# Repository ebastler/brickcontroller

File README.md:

# brickcontroller
ESP32 based PCB to control LED-bricks

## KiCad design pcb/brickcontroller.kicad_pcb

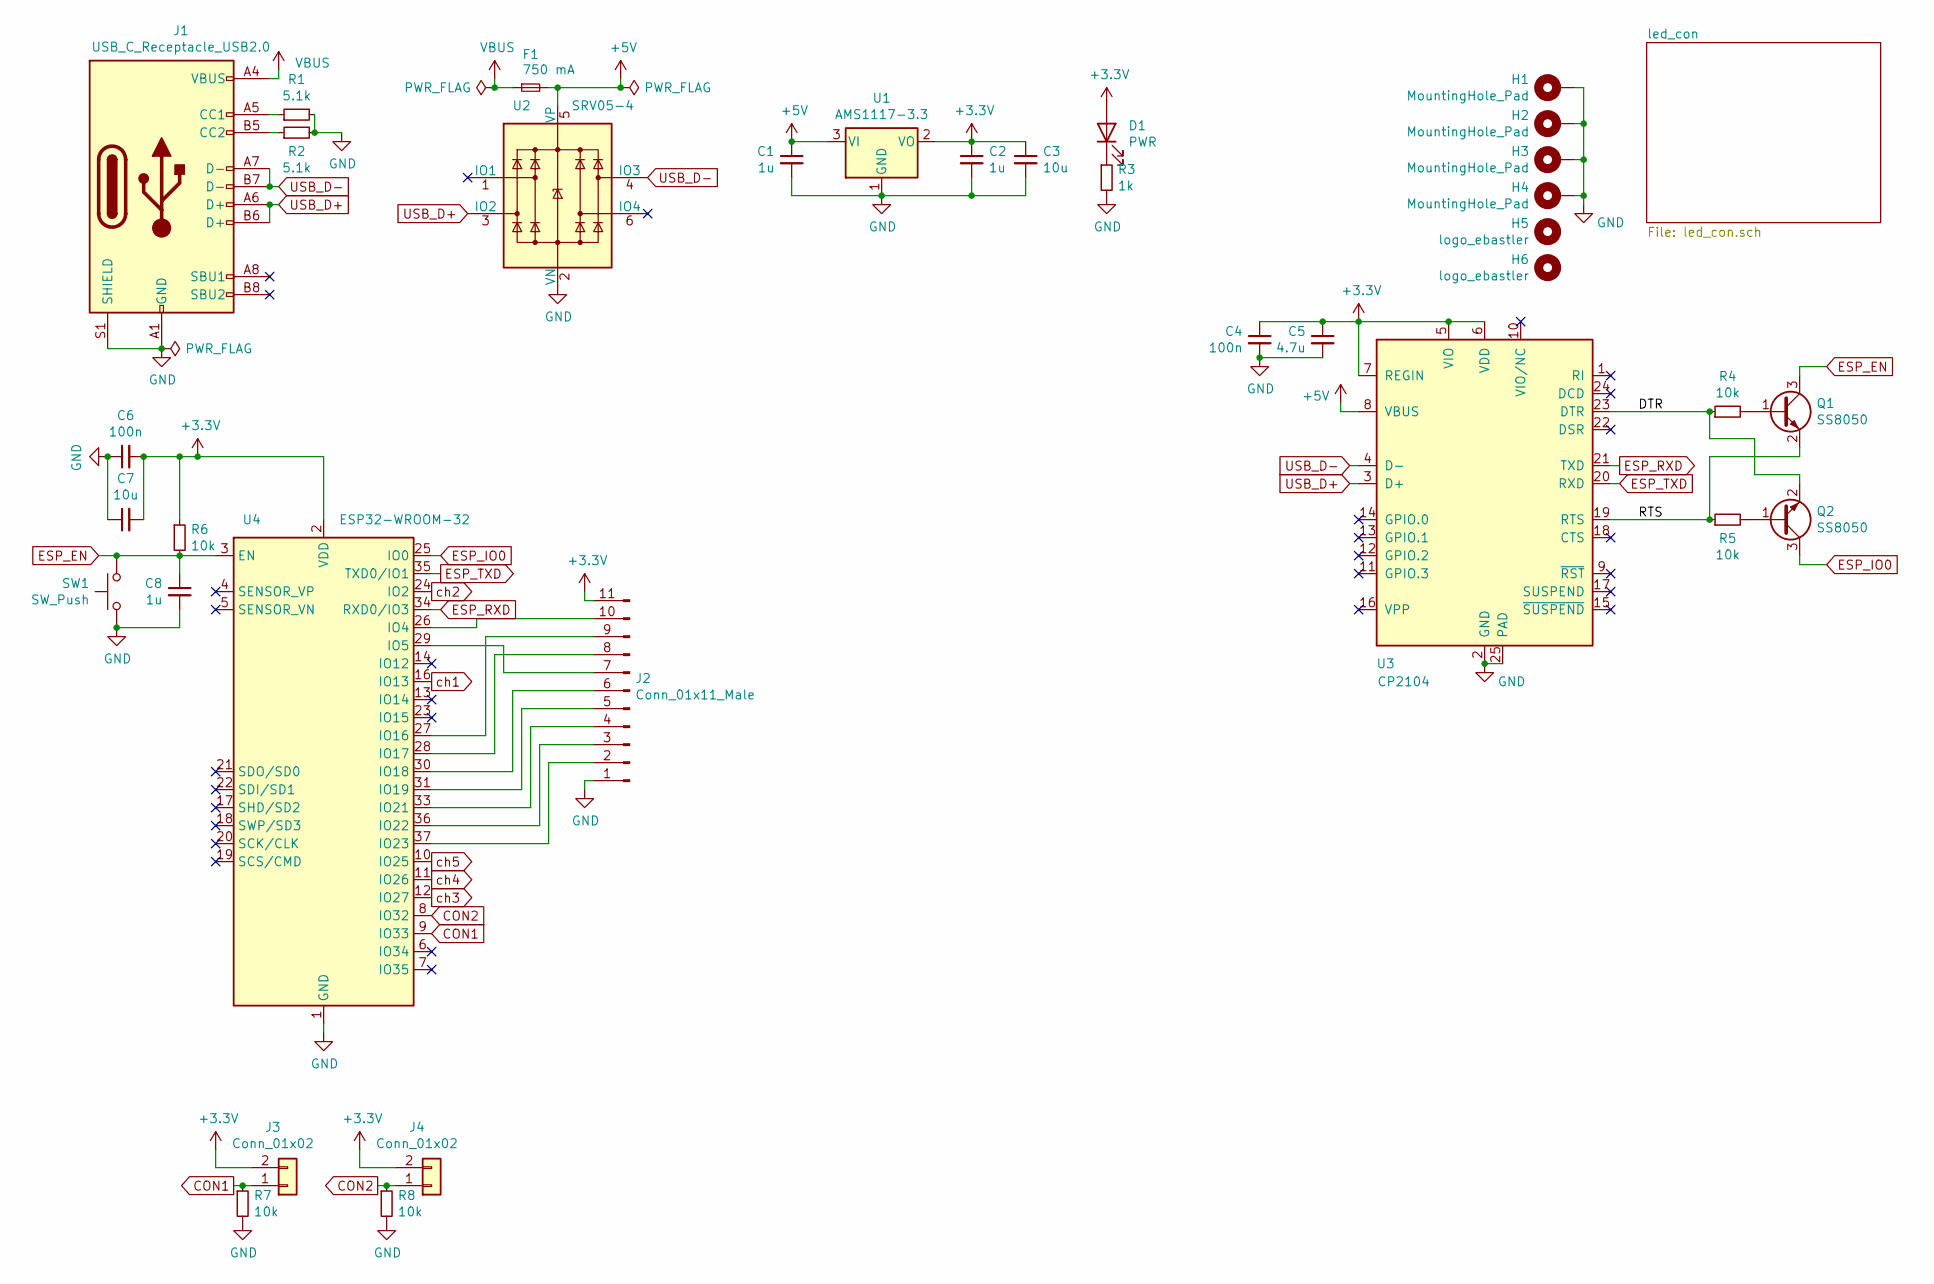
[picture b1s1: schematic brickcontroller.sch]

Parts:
C1, C2, C8: 1u; C_0603_1608Metric; LCSC C15849
C3, C7: 10u; C_0603_1608Metric; LCSC C19702
C4, C6: 100n; C_0603_1608Metric; LCSC C14663
C5: 4.7u; C_0603_1608Metric; LCSC C19666
D1: PWR; LED_0603_1608Metric; LCSC C72038
F1: 750 mA; Fuse_0603_1608Metric; LCSC C20792
H1, H2, H3, H4: MountingHole_Pad; MountingHole_3.2mm_M3_Pad_Via
H5: logo_ebastler; logo_silk_7p5
H6: logo_ebastler; brick
J1: USB_C_Receptacle_USB2.0; USB_C_Receptacle_HRO_TYPE-C-31-M-12; LCSC C165948
J2: Conn_01x11_Male; PinSocket_1x11_P2.54mm_Vertical
J3, J4: Conn_01x02; Molex_PicoBlade_53047-0210_1x02_P1.25mm_Vertical
Q1, Q2: SS8050; SOT-23; LCSC C2150
R1, R2: 5.1k; R_0402_1005Metric; LCSC C25905
R3: 1k; R_0603_1608Metric; LCSC C21190
R4, R5, R6, R7, R8: 10k; R_0603_1608Metric; LCSC C25804
SW1: SW_Push; SW_SPST_SKQG_WithoutStem; LCSC C318884
U1: AMS1117-3.3; SOT-223-3_TabPin2; LCSC C6186
U2: SRV05-4; SOT-23-6; LCSC C85364
U3: CP2104; QFN-24-1EP_4x4mm_P0.5mm_EP2.6x2.6mm; LCSC C47742
U4: ESP32-WROOM-32; LCSC C82899

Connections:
+3V3: C2.1, C3.1, C4.1, C5.1, C6.2, C7.2, D1.2 (A), J2.11, J3.2, J4.2, R6.1, U1.2 (VO), U3.5 (VIO), U3.6 (VDD), U3.7 (REGIN), U4.2 (VDD); also elsewhere on the board
+5V: C1.1, F1.2, U1.3 (VI), U2.5 (VP), U3.8 (VBUS)
/DTR: Q2.2 (E), R4.1, U3.23 (DTR)
/RTS: Q1.2 (E), R5.1, U3.19 (RTS)
CON1: J3.1, R7.1, U4.9 (IO33)
CON2: J4.1, R8.1, U4.8 (IO32)
ESP_EN: C8.1, Q1.3 (C), R6.2, SW1.2, U4.3 (EN)
ESP_IO0: Q2.3 (C), U4.25 (IO0)
ESP_RXD: U3.21 (TXD), U4.34 (RXD0/IO3)
ESP_TXD: U3.20 (RXD), U4.35 (TXD0/IO1)
GND: C1.2, C2.2, C3.2, C4.2, C5.2, C6.1, C7.1, C8.2, H1.1, H2.1, H3.1, H4.1, J1.A1 (GND), J1.A12 (GND), J1.B1 (GND), J1.B12 (GND), J1.S1 (SHIELD), J2.1, R1.2, R2.2, R3.2, R7.2, R8.2, SW1.1, U1.1 (GND), U2.2 (VN), U3.2 (GND), U3.25 (PAD), U4.1 (GND), U4.15 (GND), U4.38 (GND), U4.39 (GND); also elsewhere on the board
unnamed: D1.1 (K), R3.1
unnamed: J1.A5 (CC1), R1.1
unnamed: J1.B5 (CC2), R2.1
unnamed: J2.2, U4.37 (IO23)
unnamed: J2.3, U4.36 (IO22)
unnamed: J2.4, U4.33 (IO21)
unnamed: J2.5, U4.31 (IO19)
unnamed: J2.6, U4.30 (IO18)
unnamed: J2.7, U4.29 (IO5)
unnamed: J2.8, U4.28 (IO17)
unnamed: J2.9, U4.27 (IO16)
unnamed: J2.10, U4.26 (IO4)
unnamed: Q1.1 (B), R4.2
unnamed: Q2.1 (B), R5.2
USB_D+: J1.A6 (D+), J1.B6 (D+), U2.3 (IO2), U3.3 (D+)
USB_D-: J1.A7 (D-), J1.B7 (D-), U2.4 (IO3), U3.4 (D-)
VBUS: F1.1, J1.A4 (VBUS), J1.A9 (VBUS), J1.B4 (VBUS), J1.B9 (VBUS)
ch1: U4.16 (IO13); also elsewhere on the board
ch2: U4.24 (IO2); also elsewhere on the board
ch3: U4.12 (IO27); also elsewhere on the board
ch4: U4.11 (IO26); also elsewhere on the board
ch5: U4.10 (IO25); also elsewhere on the board

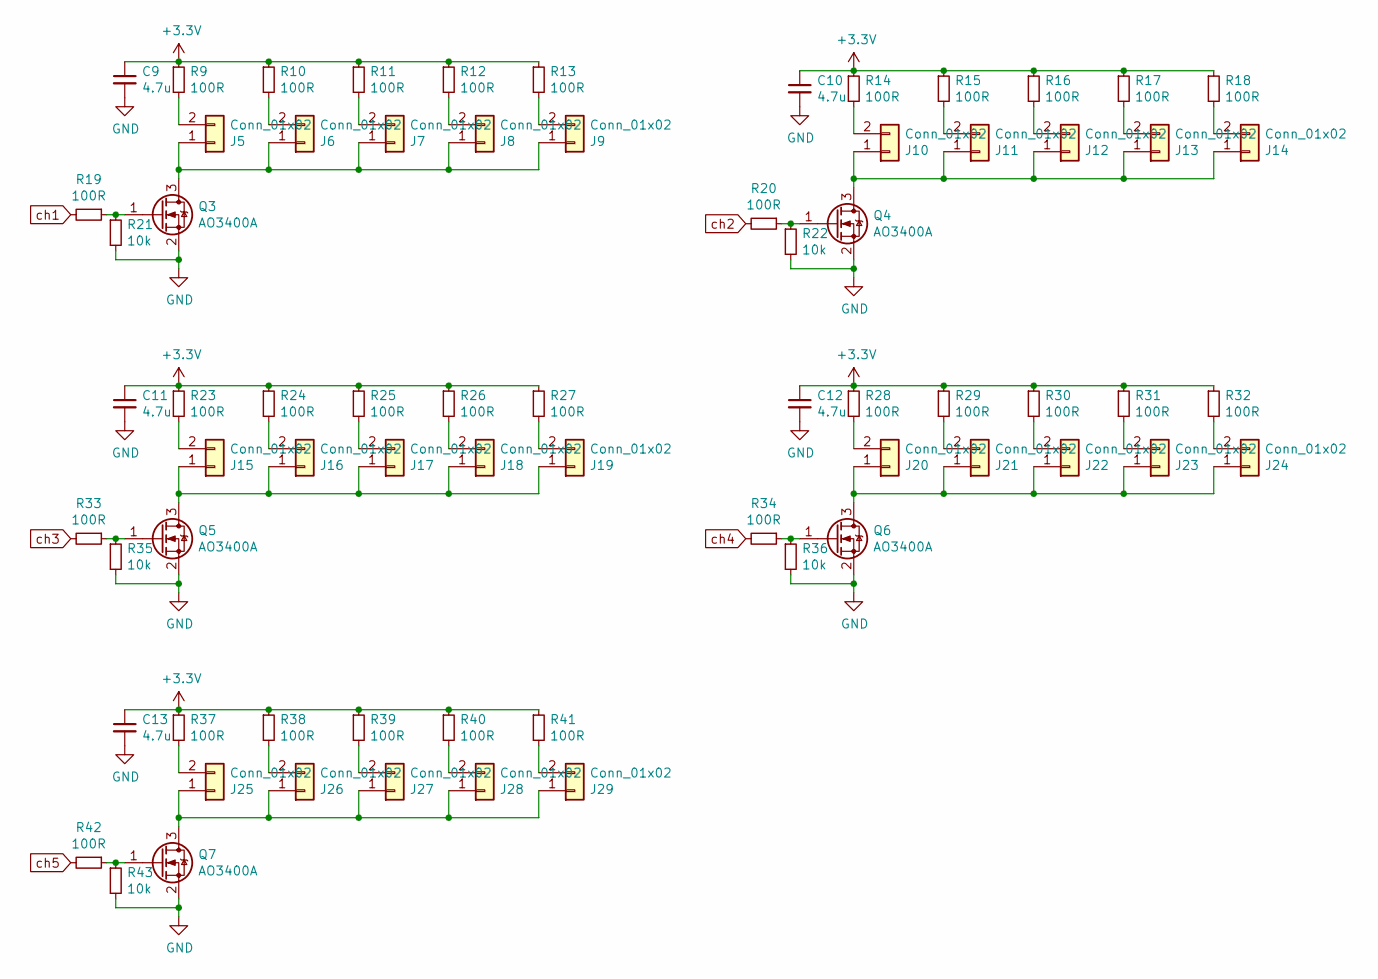
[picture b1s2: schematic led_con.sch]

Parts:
C9, C10, C11, C12, C13: 4.7u; C_0603_1608Metric; LCSC C19666
J5, J6, J7, J8, J9, J10, J11, J12, J13, J14, J15, J16, J17, J18, J19, J20, J21, J22, J23, J24, J25, J26, J27, J28, J29: Conn_01x02; Molex_PicoBlade_53047-0210_1x02_P1.25mm_Vertical
Q3, Q4, Q5, Q6, Q7: AO3400A; SOT-23; LCSC C347475
R9, R10, R11, R12, R13, R14, R15, R16, R17, R18, R19, R20, R23, R24, R25, R26, R27, R28, R29, R30, R31, R32, R33, R34, R37, R38, R39, R40, R41, R42: 100R; R_0603_1608Metric; LCSC C22775
R21, R22, R35, R36, R43: 10k; R_0603_1608Metric; LCSC C25804

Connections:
+3V3: C9.1, C10.1, C11.1, C12.1, C13.1, R9.1, R10.1, R11.1, R12.1, R13.1, R14.1, R15.1, R16.1, R17.1, R18.1, R23.1, R24.1, R25.1, R26.1, R27.1, R28.1, R29.1, R30.1, R31.1, R32.1, R37.1, R38.1, R39.1, R40.1, R41.1; also elsewhere on the board
GND: C9.2, C10.2, C11.2, C12.2, C13.2, Q3.2 (S), Q4.2 (S), Q5.2 (S), Q6.2 (S), Q7.2 (S), R21.2, R22.2, R35.2, R36.2, R43.2; also elsewhere on the board
unnamed: J5.1, J6.1, J7.1, J8.1, J9.1, Q3.3 (D)
unnamed: J5.2, R9.2
unnamed: J6.2, R10.2
unnamed: J7.2, R11.2
unnamed: J8.2, R12.2
unnamed: J9.2, R13.2
unnamed: J10.1, J11.1, J12.1, J13.1, J14.1, Q4.3 (D)
unnamed: J10.2, R14.2
unnamed: J11.2, R15.2
unnamed: J12.2, R16.2
unnamed: J13.2, R17.2
unnamed: J14.2, R18.2
unnamed: J15.1, J16.1, J17.1, J18.1, J19.1, Q5.3 (D)
unnamed: J15.2, R23.2
unnamed: J16.2, R24.2
unnamed: J17.2, R25.2
unnamed: J18.2, R26.2
unnamed: J19.2, R27.2
unnamed: J20.1, J21.1, J22.1, J23.1, J24.1, Q6.3 (D)
unnamed: J20.2, R28.2
unnamed: J21.2, R29.2
unnamed: J22.2, R30.2
unnamed: J23.2, R31.2
unnamed: J24.2, R32.2
unnamed: J25.1, J26.1, J27.1, J28.1, J29.1, Q7.3 (D)
unnamed: J25.2, R37.2
unnamed: J26.2, R38.2
unnamed: J27.2, R39.2
unnamed: J28.2, R40.2
unnamed: J29.2, R41.2
unnamed: Q3.1 (G), R19.1, R21.1
unnamed: Q4.1 (G), R20.1, R22.1
unnamed: Q5.1 (G), R33.1, R35.1
unnamed: Q6.1 (G), R34.1, R36.1
unnamed: Q7.1 (G), R42.1, R43.1
ch1: R19.2; also elsewhere on the board
ch2: R20.2; also elsewhere on the board
ch3: R33.2; also elsewhere on the board
ch4: R34.2; also elsewhere on the board
ch5: R42.2; also elsewhere on the board

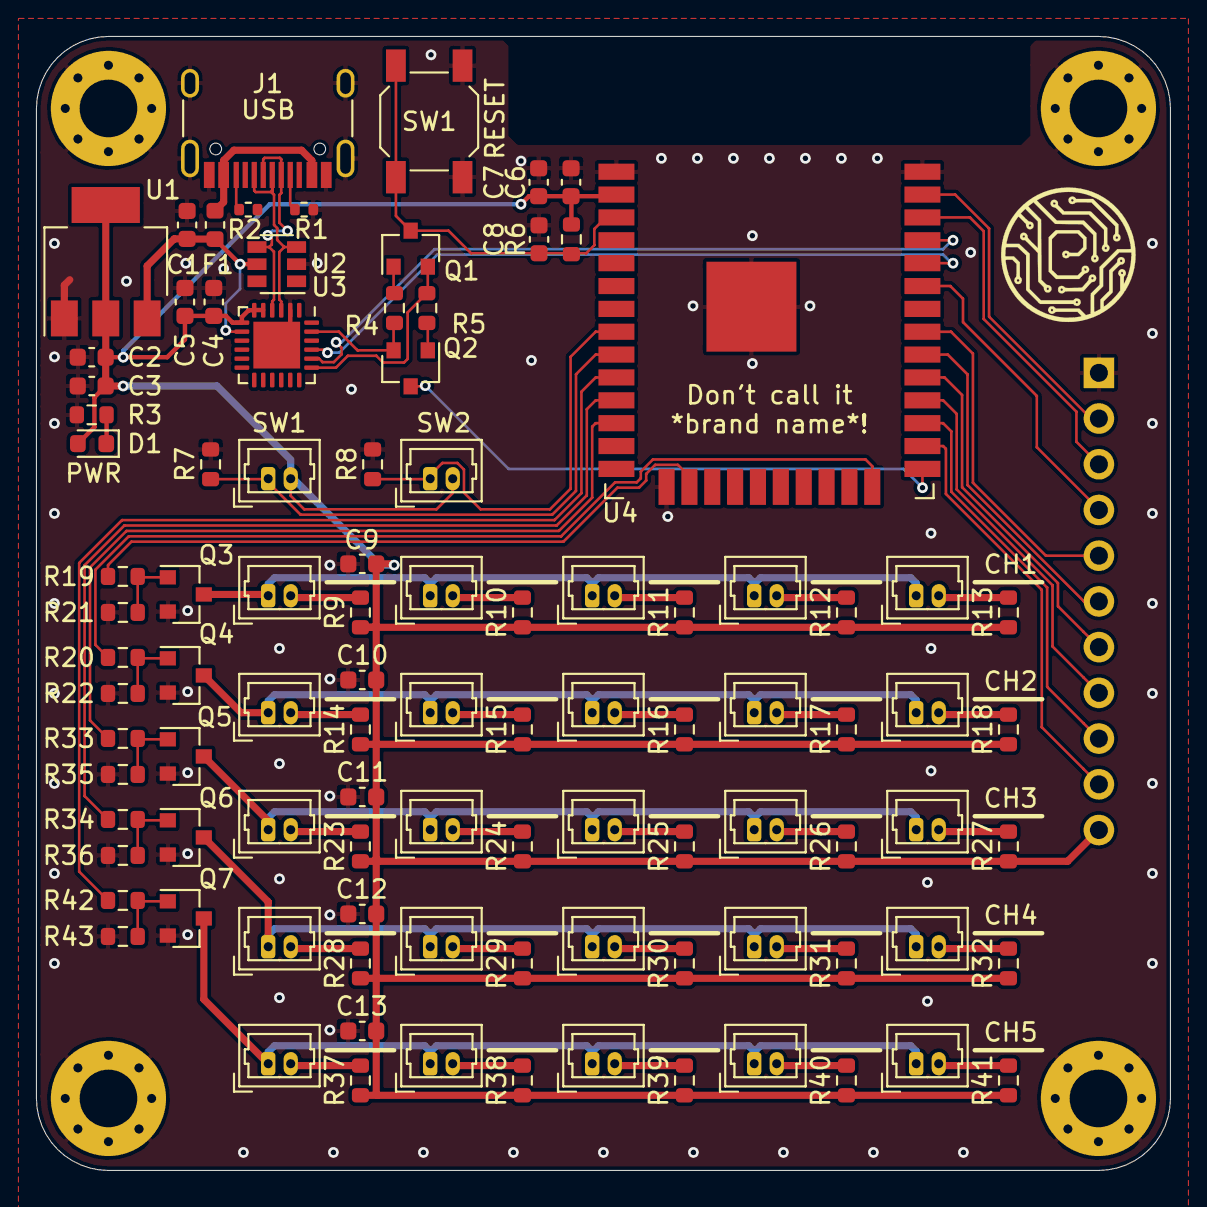
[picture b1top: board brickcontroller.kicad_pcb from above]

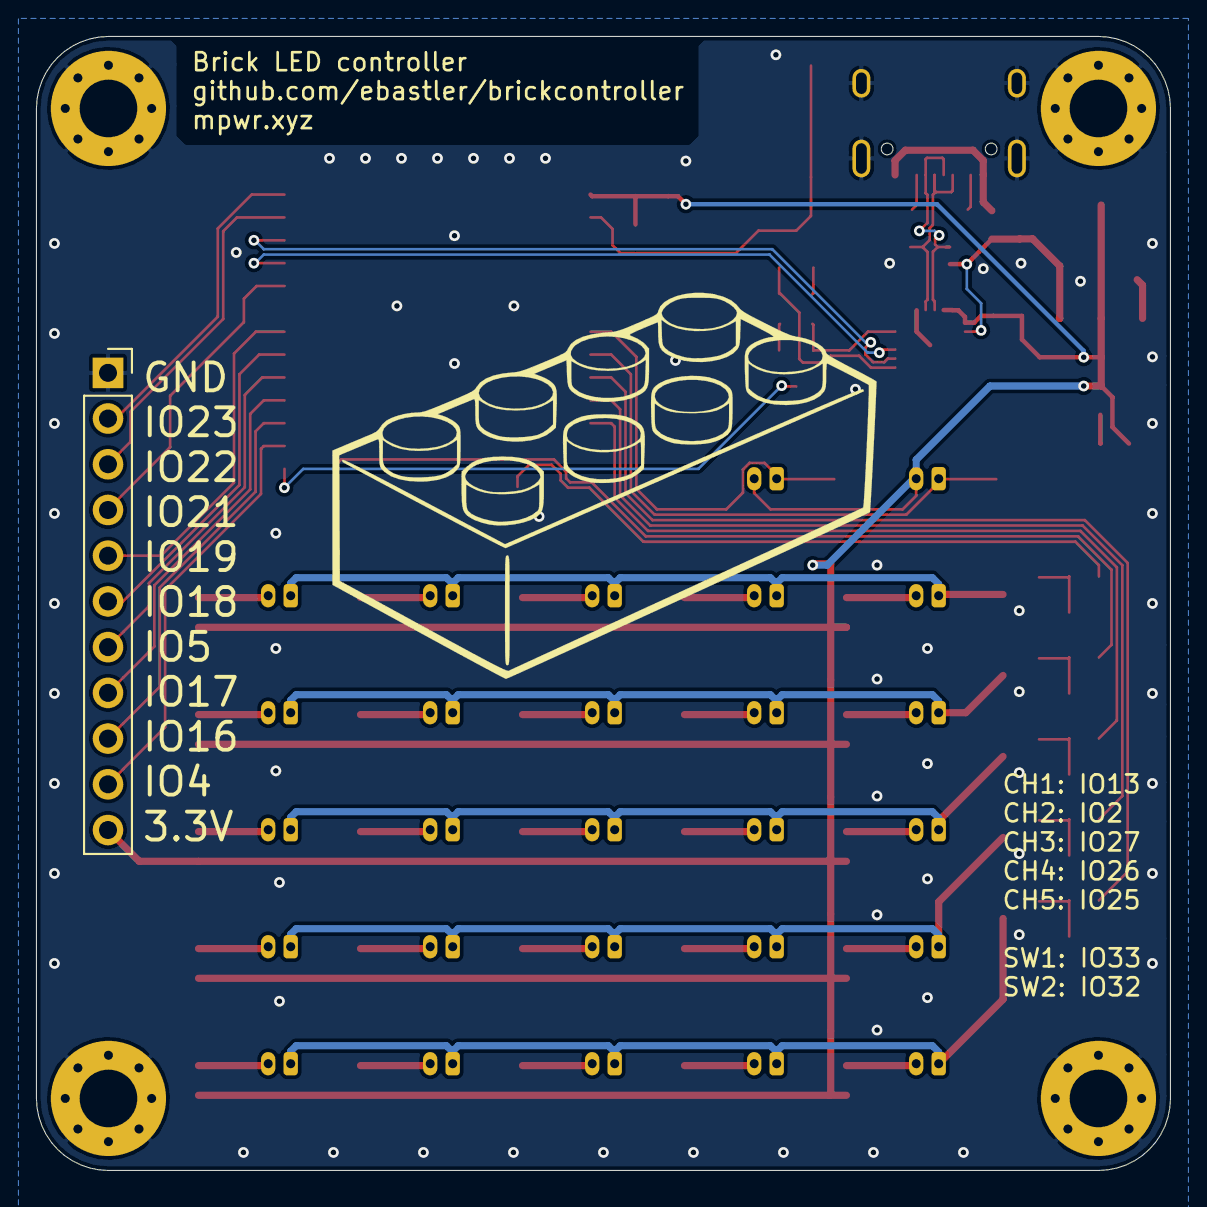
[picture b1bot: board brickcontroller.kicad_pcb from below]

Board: 2 copper layers, 63.0 x 63.0 mm, 105 parts (2 on the bottom side), 68 nets.

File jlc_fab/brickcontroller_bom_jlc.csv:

"Comment","Designator","Footprint","LCSC Part #"
"1u","C1,C2,C8","C_0603_1608Metric","C15849"
"4.7u","C5,C9,C10,C11,C12,C13","C_0603_1608Metric","C19666"
"100n","C6,C4","C_0603_1608Metric","C14663"
"10u","C7,C3","C_0603_1608Metric","C19702"
"PWR","D1","LED_0603_1608Metric","C72038"
"750 mA","F1","Fuse_0603_1608Metric","C20792"
"USB_C_Receptacle_USB2.0","J1","USB_C_Receptacle_HRO_TYPE-C-31-M-12","C165948"
"SS8050","Q1,Q2","SOT-23","C2150"
"AO3400A","Q3,Q4,Q5,Q6,Q7","SOT-23","C347475"
"5.1k","R1,R2","R_0402_1005Metric","C25905"
"1k","R3","R_0603_1608Metric","C21190"
"10k","R5,R4,R6,R7,R8,R21,R22,R36,R35,R43","R_0603_1608Metric","C25804"
"100R","R10,R11,R12,R13,R19,R14,R15,R16,R17,R18,R20,R23,R24,R25,R26,R27,R33,R28,R29,R30,R31,R32,R34,R37,R38,R39,R40,R41,R42,R9","R_0603_1608Metric","C22775"
"SW_Push","SW1","SW_SPST_SKQG_WithoutStem","C318884"
"AMS1117-3.3","U1","SOT-223-3_TabPin2","C6186"
"SRV05-4","U2","SOT-23-6","C85364"
"CP2104","U3","QFN-24-1EP_4x4mm_P0.5mm_EP2.6x2.6mm","C47742"
"ESP32-WROOM-32","U4","ESP32-WROOM-32","C82899"

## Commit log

2021-04-06 improved schematic readability
2021-04-06 added pictures
2021-04-06 added bom + cpl
